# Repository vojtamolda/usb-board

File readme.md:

# USB Measuring Board & USB Attenuator

Wouldn't be cool to drive any experiment directly from your computer? Without the need to get up from your chair and touch things? Well, now your computer can directly flip switches, measure voltages, send signals and talk to other devices using the *USB Measuring Board* or *USB Attenuator*!

If your applications is simple and requires just a few inputs and outputs then [*USB Attenuator*](/doc/attenuator.md) is the right solution. [*USB Measuring Board*](/doc/board.md) is more versatil and can handle control of more complex experiments. See [board.md](/doc/board.md) and [attenuator.md](/doc/attenuator.md) readme files for more details.

Both projects were originally inspired by the needs of the [Department of Low-Temperature Physics, Charles University, Prague](http://kfnt.mff.cuni.cz), but obviously range of application is much wider. *USB Measuring Board* was developed as part of my [bachelor thesis](/doc/thesis.pdf) written in 2009. If you're interested in how it all works, take a look at the  [prototypes](/prototypes/prototypes.md).

## Compilation
So... How do I build this monster? It's not as complicated as it looks. Build chain uses *QMake* (part of [*Qt framework*](http://qt.io)). Besides *Qt*, you'll need two libraries that provide USB communication - [*libftdi*](http://www.intra2net.com/en/developer/libftdi/index.php) and [*libusb*](http://libusb.info/). Tested platforms are Mac OS X 10.11, Ubuntu Linux 14.04 LTS and Windows 8, but chances are it would run on any platform supported by *Qt* and *libusb*.

Firmware powering the ATmega microprocessor requires it's own version C compiler, linker and standard C libraries called [*avr-toolchain*](http://savannah.nongnu.org/projects/avr-libc/). To upload the firmware no special programmer is needed. Microprocessor programming can be done over the USB cable by [*avrdude*](http://savannah.nongnu.org/projects/avrdude/).

#### Mac OS X
- Download and install latest version of *Qt* 5.x libraries from [here](http://www.qt.io/download/).
- Install *libftdi* library. [Homebrew](http://brew.sh/) installs *libusb* automatically as a dependency.
```bash
   # Get Homebrew OS X package manager here: http://brew.sh/.
   brew install libftdi
```
- Install [*avr-gcc*](https://gcc.gnu.org/wiki/avr-gcc), [*avr-libc*](http://savannah.nongnu.org/projects/avr-libc/)  and [*avrdude*](http://savannah.nongnu.org/projects/avrdude/) required to compile and upload firmware.
```bash
   # Alternatively download and install CrossPack.
   brew install avrdude
   brew tap larsimmisch/avr
   brew install avr-libc
```
- Compile both projects with *QMake* and make.
```bash
   # Alternatively open the .pro file in Qt Creator IDE.
   qmake board.pro
   qmake attenuator.pro
   cd firmware; make;
```
- Remove colliding OS X kernel extension and run the compiled application.
```bash
   # Remove AppleUSBFTDI kernel extension to prevent 'Unable to claim USB device' errors.
   sudo kextunload -bundle-id com.apple.driver.AppleUSBFTDI
```

#### Linux
- Install your distribution's default version of *Qt* 5.x libraries.
```bash
   # DEB-based distributions. (Ubuntu, Debian...)
   apt-get install qt5-default
   # RPM-based distributions. (RedHat, SUSE...)
   yum install qt5-default
```
- Install development version of *libftdi-dev* library. Package manager installs *libusb-dev* automatically as a dependency.
```bash
   # DEB-based distributions.
   apt-get install libftdi-dev
   # RPM-based distributions.
   yum install libftdi-dev
```
- Install [*avr-gcc*](https://gcc.gnu.org/wiki/avr-gcc), [*avr-libc*](http://savannah.nongnu.org/projects/avr-libc/)  and [*avrdude*](http://savannah.nongnu.org/projects/avrdude/) required to compile and upload firmware.
```bash
   # DEB-based distributions.
   apt-get install avrdude avr-gcc avr-libc
   # RPM-based distributions.
   yum install avrdude avr-gcc avr-libc
```
- Compile both projects with *QMake*.
```bash
   # Alternatively open the .pro file in Qt Creator IDE.
   qmake board.pro
   qmake attenuator.pro
   cd firmware; make
```
- Remove conflicting kernel module and run the compiled application.
```bash
   # Unload kernel module to prevent 'Unable to claim USB device' errors.
   sudo rmmod ftdi_sio
```

#### Windows
- Download and install latest version of *Qt* 5.x libraries from [here](http://www.qt.io/download/).
- Download and compile libraries required for USB communication.
  - Source code and documentation for *libusb* is available [here](http://github.com/libusb/libusb/)
  - Source code and documentation for *libftdi* is available [here](http://www.intra2net.com/en/developer/libftdi/repository.php).
  - Copy freshly compiled static libraries and headers (*ftdi.h*, *usb.h*, *libftdi.lib* and *libusb.lib*) into *lib/win32/*.
- Download and install [*WinAVR*](http://winavr.sourceforge.net/) required to compile and upload firmware.
- Compile both projects with *QMake*.
```bat
   :: Alternatively open the .pro file in Qt Creator IDE.
   qmake.exe board.pro
   qmake.exe attenuator.pro
   cd firmware; make.exe
```

## Schematics and PCB Layouts
Circuit schematics (.sch) and PCB layouts (.brd) files are designed with [Eagle CAD](http://www.cadsoftusa.com/). Free version for non-commercial use version can be downloaded [here](http://www.cadsoftusa.com/download-eagle/).

## License
This work is licensed under the [GNU GPL 3.0 License](http://www.gnu.org/licenses/gpl-3.0.html) © 2009.

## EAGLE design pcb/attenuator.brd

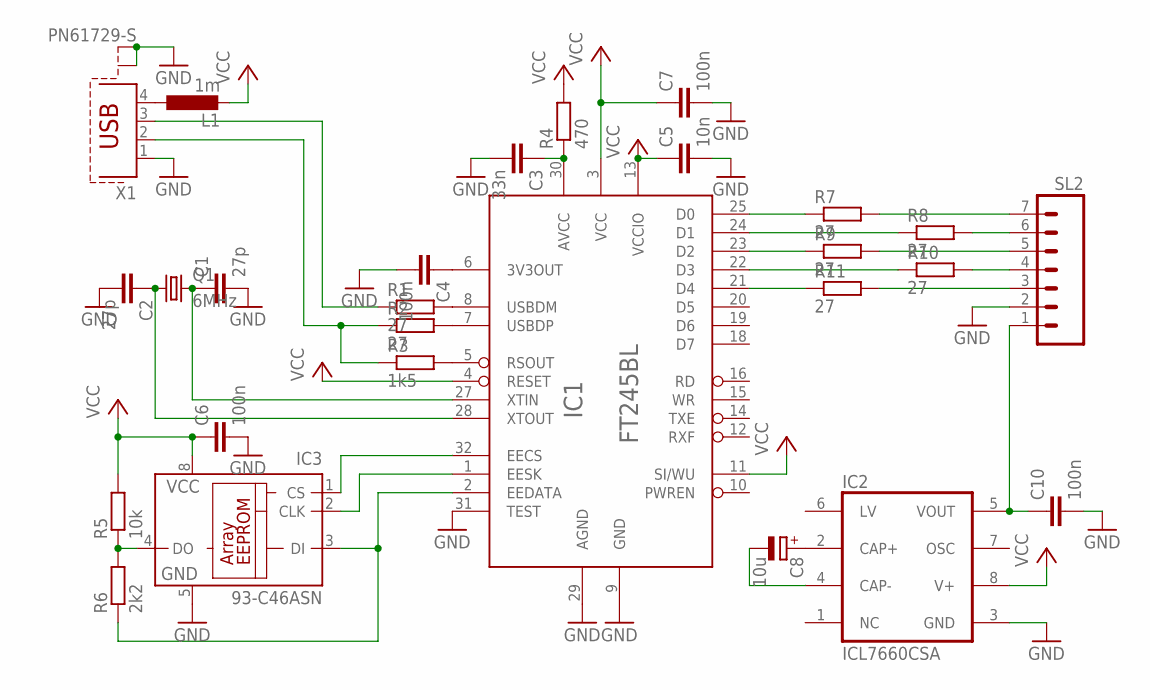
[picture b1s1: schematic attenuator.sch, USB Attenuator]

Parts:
C1, C2: 27p; C0805
C3: 33n; C0805
C4, C6, C7, C10: 100n; C0805
C5: 10n; C0805
C8: 10u; SMC_C
IC1: FT245BL; LQFP32
IC2: ICL7660CSA; SO08
IC3: 93-C46ASN; SO-08
L1: 1m; M0805
Q1: 6MHz; HC49U70
R1, R2, R7, R8, R9, R10, R11: 27; M0805
R3: 1k5; M0805
R4: 470; M0805
R5: 10k; M0805
R6: 2k2; M0805
SL2: MA07; 07PA
X1: PN61729-S

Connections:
GND: C1.2, C2.2, C3.2, C4.2, C5.2, C6.2, C7.2, C10.2, IC1.9 (GND), IC1.17 (GND), IC1.29 (AGND), IC1.31 (TEST), IC2.3 (GND), IC3.5 (GND), SL2.2, X1.1, X1.S1, X1.S2
unnamed: C1.1, IC1.27 (XTIN), Q1.2
unnamed: C2.1, IC1.28 (XTOUT), Q1.1
unnamed: IC1.32 (EECS), IC3.1 (CS)
unnamed: IC1.1 (EESK), IC3.2 (CLK)
unnamed: IC1.2 (EEDATA), IC3.3 (DI), R6.1
unnamed: R7.2, SL2.7
unnamed: IC3.4 (DO), R5.1, R6.2
unnamed: C8.+, IC2.2 (CAP+)
unnamed: R2.1, R3.1, X1.2
unnamed: R1.1, X1.3
unnamed: IC1.7 (USBDP), R2.2
unnamed: IC1.8 (USBDM), R1.2
unnamed: C4.1, IC1.6 (3V3OUT)
unnamed: C8.-, IC2.4 (CAP-)
unnamed: L1.1, X1.4
unnamed: R8.2, SL2.6
unnamed: R9.2, SL2.5
unnamed: IC1.22 (D3), R10.1
unnamed: IC1.21 (D4), R11.1
unnamed: IC1.25 (D0), R7.1
unnamed: IC1.24 (D1), R8.1
unnamed: IC1.23 (D2), R9.1
unnamed: R10.2, SL2.4
unnamed: R11.2, SL2.3
unnamed: C10.1, IC2.5 (VOUT), SL2.1
unnamed: C3.1, IC1.30 (AVCC), R4.1
RSOUT: IC1.5 (RSOUT), R3.2
VCC: C5.1, C6.1, C7.1, IC1.3 (VCC), IC1.4 (RESET), IC1.11 (SI/WU), IC1.13 (VCCIO), IC1.26 (VCC), IC2.8 (V+), IC3.8 (VCC), L1.2, R4.2, R5.2

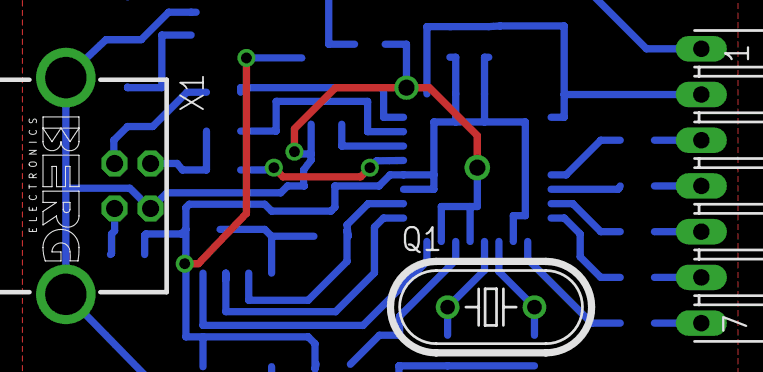
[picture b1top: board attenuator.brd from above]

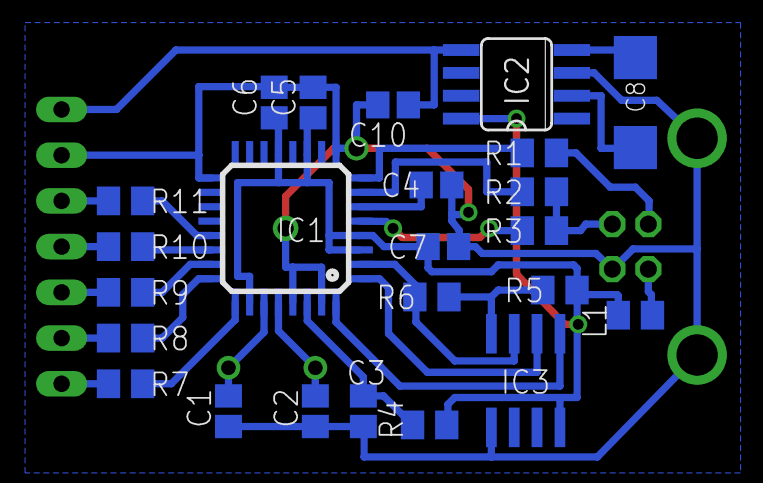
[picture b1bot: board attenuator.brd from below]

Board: 2 copper layers, 27 parts (24 on the bottom side), 29 nets.

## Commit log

2015-12-05 Documentation, Thesis & License
2015-12-05 Initialize Repository
2015-12-05 Prototypes
2015-12-05 Schematics & Printed Circuit Boards
2015-12-05 Desktop Application Source Code
2015-12-05 ATmega Firmware Source Code
